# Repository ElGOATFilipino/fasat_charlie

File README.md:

# FASat_charlie macropad
This is a macropad in the shape of the chilean satelite FASat-CHARLIE. It has 6 keys with a rotary encoder, 16 SK6812MINI-E leds on the edges of its pcb and uses kmk firmware.

I made this macropad to help me open the websites I need for school instantly, to record as well as mute! (Since I costantly forget the keybinds for those).

## Features: 
- 16 SK6812MINI-E leds, all used for as a "glow" that the macropad emanates in the dark!
- EC11 Rotary encoder /w switch for adjusting led colors and brightness
- 6 keys
- Shape of the FASat-CHARLIE satelite

## CAD
The entire case uses 6 M3x16mm bolts and M3 headseat inserts (4mm deep). 4 are screwed from under the case and the other 2 are used to join the "flag".

The case has 3 separate 3d printed pieces. The bottom, which has a 16 degree inclination so it can face me once I lay it flat on a surface. It also has info. about the satelite on the back. 
The top exposes the pcb so the leds can be seen and has a circular hole where the buttons and rotary encoder will be. 
Lastly, the flag is just a decorative piece that contains acknowlegements.

Here's how it'll all fit together

*All made in Fusion 360, the model is too big so I had to compress it into a zip file.

## PCB
The pcb was made in KiCAD! I had a lot of fun using this software for my pcb, I think i'll be using it for future projects!

Schematic

PCB (It contains a lot of errors, since the DRC thinks that the edge.cuts on the leds is not supposed to be there, but it is).

## Firmware features (not required, but still good to add!)
- Rotary encoder can adjust the brightness of leds. If the button is pressed it turn the leds red, orange, yellow, green, blue, purple, make them do a rainbow animation and finally, off. (Example: if I press the button 4 times, the leds turn green.)
- Four of the keys open Turbo.ai, Canva, Word, Google classroom. The other two start recording on my computer and mute volume.

## BOM
Here are all the parts needed to make my macropad!

- x6 MX-Style switches (Cherry)
- x6 DSA keycaps (1u)
- x6 M3x16mm SHCS bolts
- x4 M3x5x4 headseat inserts
- x16 SK6812MINI-E LEDs
- x1 EC11 Rotary Encoder
- x1 XIAO RP2040-DIP
- x1 Case (3 3d printed parts)

## Fun facts:
- It was supposed to be in the shape of the sojourner rover (which took me 2 weeks to complete), but it was to big and ugly.
- I was inspired to make it in the shape of the FASat-CHARLIE when I saw a replica of it at Santiago's National Museum of Aeronautics and space.

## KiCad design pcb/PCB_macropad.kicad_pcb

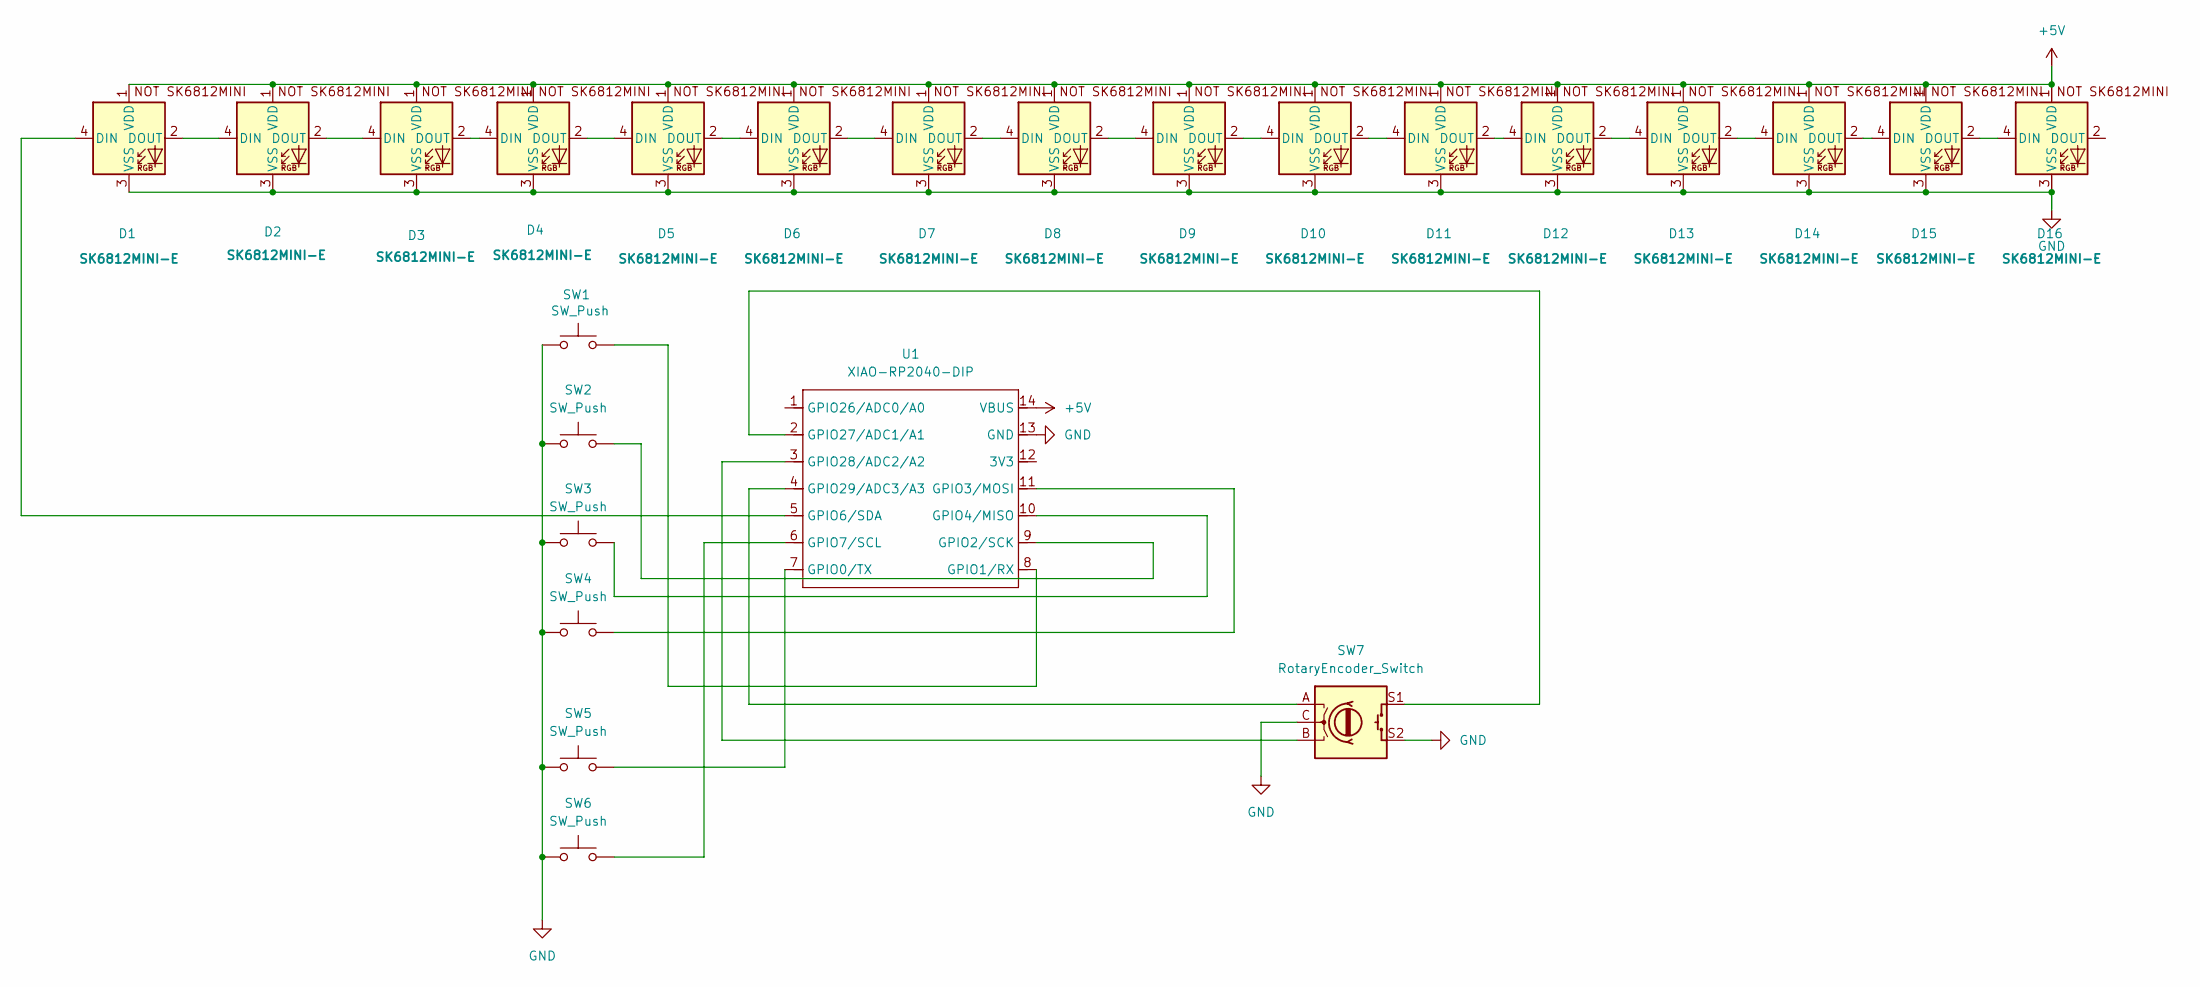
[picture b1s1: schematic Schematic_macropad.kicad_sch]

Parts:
D1, D2, D3, D4, D5, D6, D7, D8, D9, D10, D11, D12, D13, D14, D15, D16: SK6812MINI-E; SK6812MINI-E_fixed
SW1, SW2, SW3, SW4, SW5, SW6: SW_Push; SW_Cherry_MX_1.00u_PCB
SW7: RotaryEncoder_Switch; RotaryEncoder_Alps_EC11E-Switch_Vertical_H20mm
U1: XIAO-RP2040-DIP; XIAO-Generic-Hybrid-14P-2.54-21X17.8MM

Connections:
+5V: D1.1 (VDD), D2.1 (VDD), D3.1 (VDD), D4.1 (VDD), D5.1 (VDD), D6.1 (VDD), D7.1 (VDD), D8.1 (VDD), D9.1 (VDD), D10.1 (VDD), D11.1 (VDD), D12.1 (VDD), D13.1 (VDD), D14.1 (VDD), D15.1 (VDD), D16.1 (VDD), U1.14 (VBUS)
GND: D1.3 (VSS), D2.3 (VSS), D3.3 (VSS), D4.3 (VSS), D5.3 (VSS), D6.3 (VSS), D7.3 (VSS), D8.3 (VSS), D9.3 (VSS), D10.3 (VSS), D11.3 (VSS), D12.3 (VSS), D13.3 (VSS), D14.3 (VSS), D15.3 (VSS), D16.3 (VSS), SW1.1, SW2.1, SW3.1, SW4.1, SW5.1, SW6.1, SW7.C, SW7.S2, U1.13 (GND)
unnamed: D1.4 (DIN), U1.5 (GPIO6/SDA)
unnamed: D1.2 (DOUT), D2.4 (DIN)
unnamed: D2.2 (DOUT), D3.4 (DIN)
unnamed: D3.2 (DOUT), D4.4 (DIN)
unnamed: D4.2 (DOUT), D5.4 (DIN)
unnamed: D5.2 (DOUT), D6.4 (DIN)
unnamed: D6.2 (DOUT), D7.4 (DIN)
unnamed: D7.2 (DOUT), D8.4 (DIN)
unnamed: D8.2 (DOUT), D9.4 (DIN)
unnamed: D9.2 (DOUT), D10.4 (DIN)
unnamed: D10.2 (DOUT), D11.4 (DIN)
unnamed: D11.2 (DOUT), D12.4 (DIN)
unnamed: D12.2 (DOUT), D13.4 (DIN)
unnamed: D13.2 (DOUT), D14.4 (DIN)
unnamed: D14.2 (DOUT), D15.4 (DIN)
unnamed: D15.2 (DOUT), D16.4 (DIN)
unnamed: SW5.2, U1.7 (GPIO0/TX)
unnamed: SW1.2, U1.8 (GPIO1/RX)
unnamed: SW2.2, U1.9 (GPIO2/SCK)
unnamed: SW4.2, U1.11 (GPIO3/MOSI)
unnamed: SW3.2, U1.10 (GPIO4/MISO)
unnamed: SW6.2, U1.6 (GPIO7/SCL)
unnamed: SW7.S1, U1.2 (GPIO27/ADC1/A1)
unnamed: SW7.B, U1.3 (GPIO28/ADC2/A2)
unnamed: SW7.A, U1.4 (GPIO29/ADC3/A3)

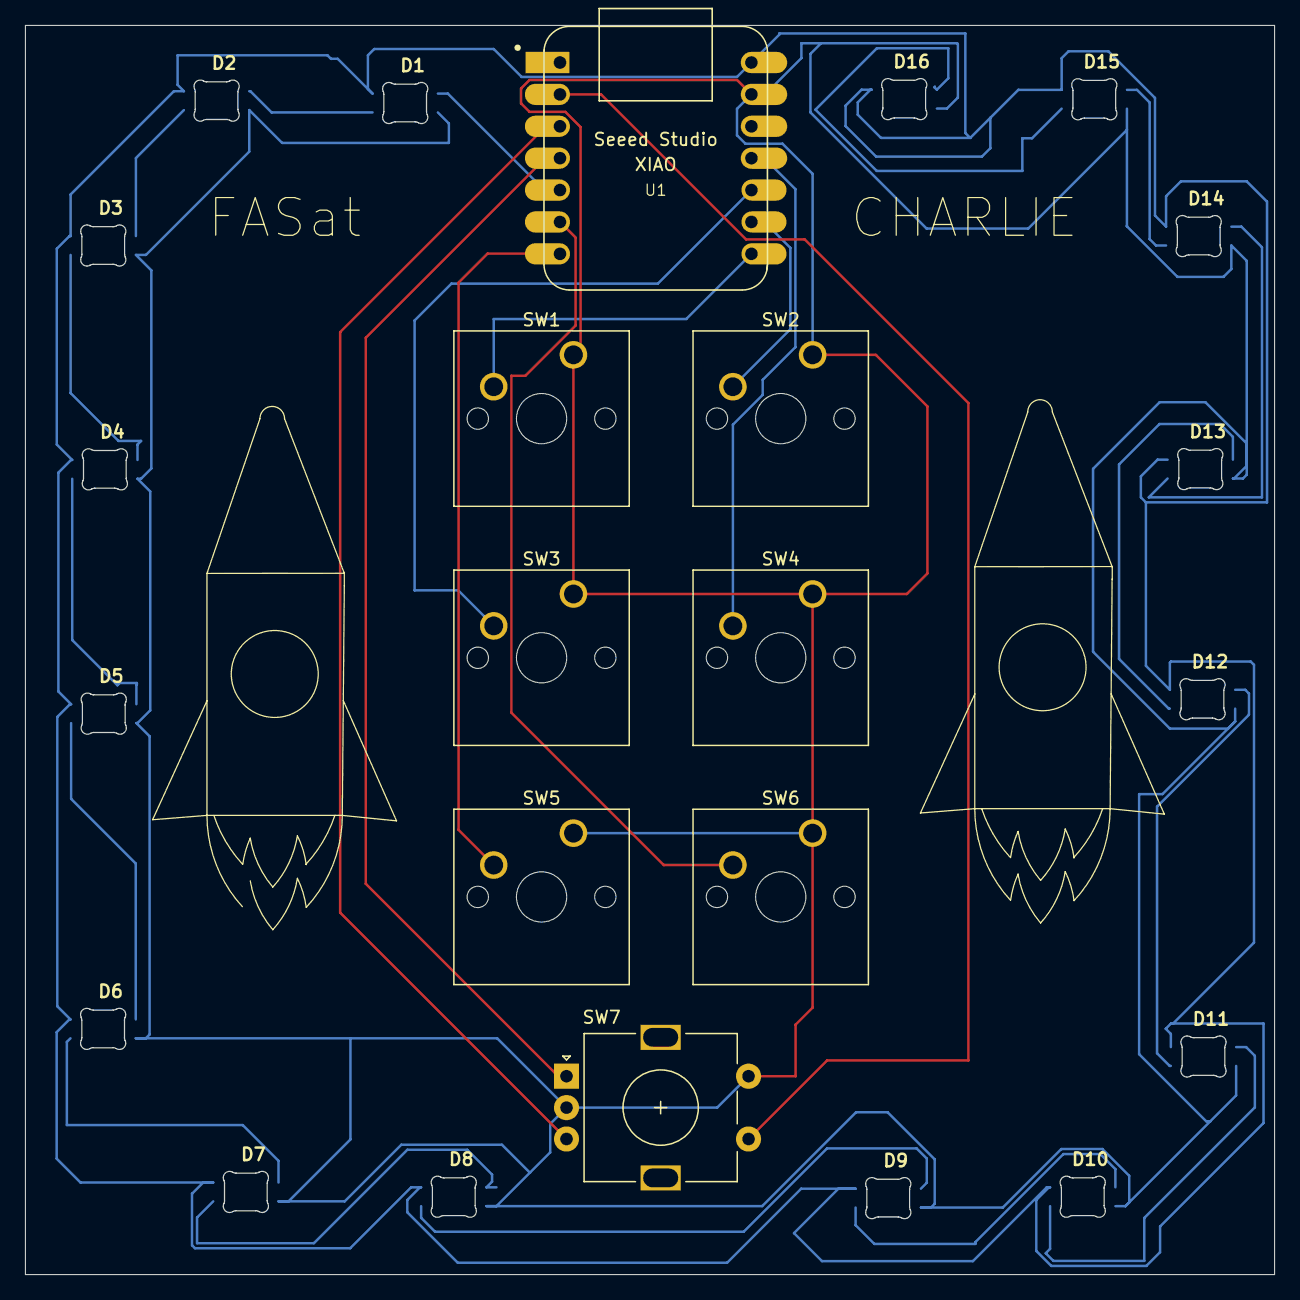
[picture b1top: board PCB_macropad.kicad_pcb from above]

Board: 2 copper layers, 99.5 x 99.4 mm, 24 parts (0 on the bottom side), 27 nets.

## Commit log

2026-02-07 Update README with project details and features
    Added project description and features to README.
2026-02-07 Fix typos and enhance README content
    Corrected typos and improved clarity in the README.
2026-02-07 Fix project name capitalization and formatting in README
    Corrected the capitalization of the project name and fixed some formatting issues in the README.
2026-02-07 Fix typos and enhance clarity in README.md
    Corrected typos and improved sentence structure in the README.
2026-02-07 Fix capitalization and enhance README content
    Corrected capitalization and formatting issues throughout the README. Added details about the PCB and firmware features.
2026-02-07 Modify README title for clarity
    Updated project title to include 'macropad'.
2026-02-08 Clarify Fusion 360 model size in README
    Added clarification about the Fusion 360 model size and compression.
